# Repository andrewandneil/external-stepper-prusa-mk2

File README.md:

# External Stepper Drivers for Prusa MK2 Based Printers
Adds the ability to use external TMC stepper drivers on the Prusa MK2/S/2.5/S (any printer that uses the Mini Rambo).

## Purpose
Since the Mini Rambo that powers the original line of Prusas was released, stepper driver technology has come a long way. Now days, the `A4982`s that are hard soldered onto the board are louder and less accurate than more modern offerings from `Trinamic`.

The mission of this project is to create an open source PCB ~~and Case~~ design to allow the use of standard, off the shelf stepper driver boards to be used with printers such as the `Prusa MK2/S/2.5/S`. This will allow the printer to run quieter and smoother, resulting in a nicer experience whilst printing, as well as a nicer quality of print.

Achived by utilising the handily placed test points on the back of the Mini Rambo, this board is able to 'steal' the data signals intended for the `A4982`s on the board and give them to the user's choice of stepper drivers.

Side note: if you have a blown driver on your Mini Rambo, this is a great way of getting it up and running again. Simiply solder this board to the pads corresponding to the dead driver on the back of the board, and hey presto, a functional printer again!

Upon seeing a certain other design on the internet that did the same thing, but was closed source, I decided to create my own design from scratch, and make it open source! You will find all KiCAD PCB Design files, along with the F3D files and STEP files for the case I have created. 

## Functionality
Tested mostly with the `TMC2208` drivers, however, `TMC2209`s, `TMC2130`s and `TMC2100`s (may require to be in their 'standalone' mode) have all been tested and confirmed to work with this board and the printer. However, do note the graphic towards the bottom left of the PCB for the correct positioning of the jumpers for your stepper drivers.

Compatible with any printer using the Mini Rambo main board, including but not limited to `Prusa i3 MK2`, `Prusa i3 MK2S`, `Prusa i3 MK2.5` and `Prusa i3 MK2.5S`.

## Utilisation
This WILL require modifying your mainboard. However, the modification is not permant and can be reversed at any time. Only requires soldering to 8 fairly large points on the back of the main board. You will also need to get power for the board from somewhere. To do this you have 2 options:
  1. Tap into the 12V supplied from the printer's power supply and run a cable to the socket on the board.
  2. Run either a 12V or 24V external power supply and utilise that. 

The 24V option is your prefered option if you are wanting the drivers to operate as cool and quite as possible, however, please see the [optional](/Guides/PartsList.md/#optional) section of the parts list for more information.

#### Setting Stepper Current
My `TMC2208`s have been set to a Vref voltage of 1V[^1].

## What's Included?
In the repository you will find the KiCAD files if you wish to modify, adapt or improve the board ~~and a 3D printable case for the board, along with a STEP file if you wish to modify, adapat or improve it.~~ (yet to be added).

Please see the [releases](https://github.com/andrewandneil/external-stepper-prusa-mk2/releases) section to find the current Gerber files for the fabrication of the PCB.

## Software Used
  - [KiCAD](https://kicad.org): An amazing, open source, PCB design studio. I encourage you to check it out if you're looking for something like that. Used to design the schematics, PCB and export the Gerber Files.
  - [Fusion 360](https://www.autodesk.com/products/fusion-360): A good all round CAD software, with a free personal license. ~~Used to design the case.~~

## Pictures
To be added

## Cases

### My Case
As of the moment yet to be finalised

### Other People's Cases
In the offchance that someone either, modifies, redesigns, or creates from sctach a new case or related accessory, I'll do my best to add them here.

If you're one of amazing community that might create a case, get in touch with me and I'll link it here, along with any credit due.

## Parts List
Please see [here](/Guides/PartsList.md).

## Assembly Guide
Please see [here](/Guides/AssemblyGuide.md).

## What else
Notice how nowhere in this guide I mentioned the X and Y axis until now? Well, for good reason. If you wanted to you could build a board for the E and Z axis and use it in parallel to a X and Y board (or just use the E and Z board if you're weird like that I suppose). The Z motor plug will need to be split into 2 new plugs (one for ZL and ZR). The board labels the two sockets with X and Y identifiers, but this is more so you can trace which plug goes where. Obvisouly just connect either the X or Y plugs to the E or Z solder pads on the Rambo if you're planning on doing this.

However, logically with the X and Y axis doing the most moving and at the highest speeds, your best bet to make it mostly quiet is just making one for the X and Y.

## Future Plans
I have no clue if I will ever get around to implementing these plans but you might as well know about them (if I don't do them and you're reading this in the future please feel free to 'borrow' these ideas 😉):
  - Creating a board that allows X, Y, E and Z axis drivers all on one board.
  - Creating a 3D printable case for the board.
  - Test the board with even more drivers.
  - Create an easy to follow and detailed guide for assembly.

## Using these Files
This project is protected by a GNU GPL v3.0 license:
  - You are free to use the files and designs to create your own boards in a personal manner[^2].
  - You are also free to use the files and designs to create boards to sell and make a profit, so long as credit is given or a link is added to this GitHub page[^2].
  - You are also free to modify or otherwise change the files and designs included in anyway you see fit, so long as if the project is shared, it follows the GNU GPL v3.0 license and credit is given[^2].

I fully encourage you to do what you see fit with this design, so long as it follows the GNU license[^2]. If you have the know how and have an idea for an improvement, I look forward to see what you can do! After all, that's the spirit of RepRap!

[^2]:**Not legal adivce. Please read [COPYING.txt](/COPYING.txt) for the full GNU GPL v3.0 license**

## Currently Known Issues
##### Will do my best to update if other issues are found
  - Z and E motors will 'squeal' if using TMC drivers on X and Y axis. I believe this to be something to do with microstepping. Only happens if the motors are powered and at a certain rotational degree. *Your quick fix here is to ignore it or make a board for the E and Z axis*
    - It is completely unnoticable during motion. You will only really hear it if your printer is unlucky enough to stop in a rotaional positon where it happens.

## Disclamer
I have tested this board extensively and have yet to run into issues, however, if you choose to do this mod, you do so at your own risk. I, nor any other party involved, offer any kind of warranty with this product. I have done my best to include all relevant information in this GitHub page, to allow you to come to a decision as to wether or not you would like to partake in this mod. This is not a product. You must source and assemble the board yourself. I will do my best to support any issues you may have if I can.

[^1]: My reference voltage and therefore stepper current is just a suggestion not a defintive do it. Do your own research and experimentation to suit your steppers and drivers.

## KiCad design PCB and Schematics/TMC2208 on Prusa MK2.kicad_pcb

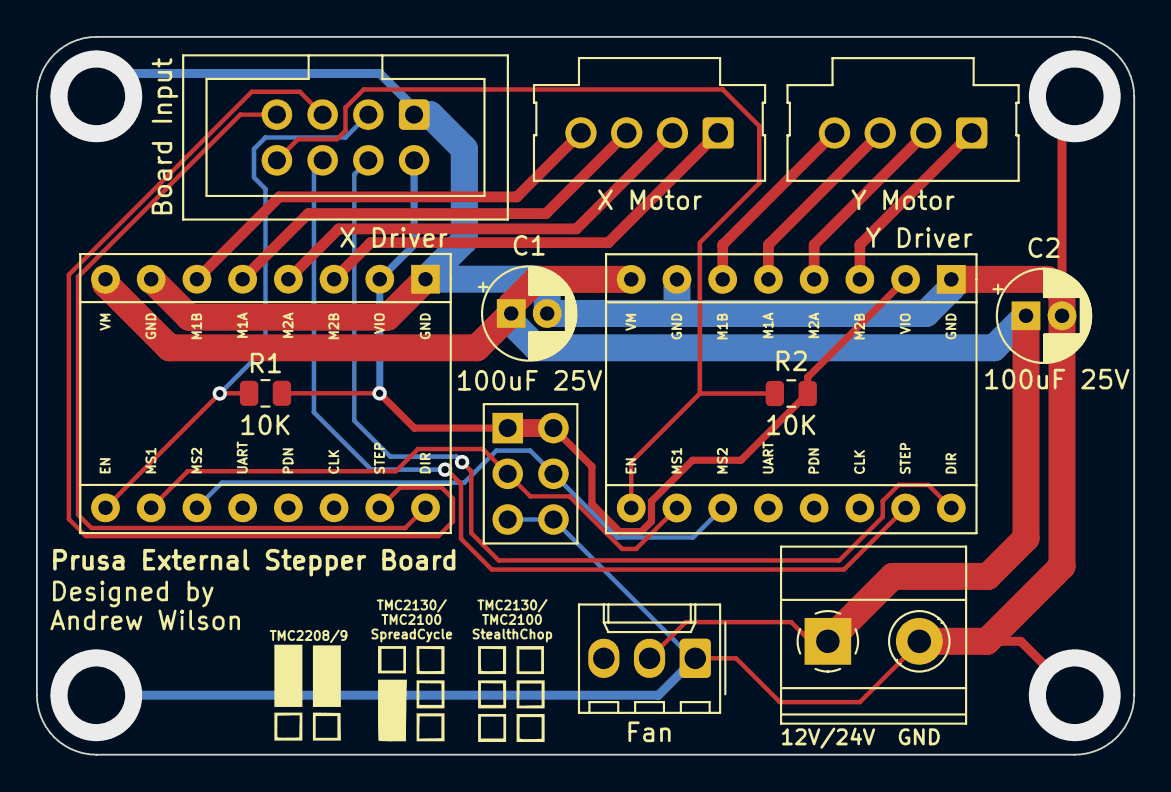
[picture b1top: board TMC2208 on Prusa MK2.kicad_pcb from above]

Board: 2 copper layers, 61.0 x 39.9 mm, 12 parts (0 on the bottom side), 19 nets.

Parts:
Board Input: Conn_02x04_Odd_Even; IDC-Header_2x04_P2.54mm_Vertical
C1, C2: 100uF 25V; CP_Radial_D5.0mm_P2.00mm
Fan: Conn_01x03_Male; Molex_KK-254_AE-6410-03A_1x03_P2.54mm_Vertical
J1: Conn_02x03_Counter_Clockwise; PinHeader_2x03_P2.54mm_Vertical
J4: Screw_Terminal_01x02; TerminalBlock_Phoenix_MKDS-1,5-2-5.08_1x02_P5.08mm_Horizont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
R1, R2: 10K; R_0805_2012Metric
X Motor: Conn_01x04_Male; Molex_SL_171971-0004_1x04_P2.54mm_Vertical
XDriver1: Trinamic_Breakout_TMC2208; Trinamic_Breakout-16_15.2x20.3mm
Y Motor: Conn_01x04_Male; Molex_SL_171971-0004_1x04_P2.54mm_Vertical
YDriver1: Trinamic_Breakout_TMC2208; Trinamic_Breakout-16_15.2x20.3mm

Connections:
+12V: C1.1, C2.1, Fan.2, J4.1, XDriver1.8 (VM), YDriver1.8 (VM)
/CONFIG1: J1.3, XDriver1.10 (MS1), YDriver1.10 (MS1)
/CONFIG2: J1.4, XDriver1.11 (MS2), YDriver1.11 (MS2)
GND: Board Input.1, C1.2, C2.2, Fan.1, J1.5, J1.6, J4.2, XDriver1.1 (GND), XDriver1.7 (GND), YDriver1.1 (GND), YDriver1.7 (GND)
unnamed: Board Input.3, R1.1, XDriver1.9 (~ENABLE)
unnamed: Board Input.4, YDriver1.16 (DIR)
unnamed: Board Input.5, XDriver1.15 (STEP)
unnamed: Board Input.6, YDriver1.15 (STEP)
unnamed: Board Input.7, XDriver1.16 (DIR)
unnamed: Board Input.8, R2.2, YDriver1.9 (~ENABLE)
unnamed: X Motor.1, XDriver1.3 (M2B)
unnamed: X Motor.2, XDriver1.4 (M2A)
unnamed: X Motor.3, XDriver1.5 (M1A)
unnamed: X Motor.4, XDriver1.6 (M1B)
unnamed: Y Motor.1, YDriver1.3 (M2B)
unnamed: Y Motor.2, YDriver1.4 (M2A)
unnamed: Y Motor.3, YDriver1.5 (M1A)
unnamed: Y Motor.4, YDriver1.6 (M1B)
VCC: Board Input.2, J1.1, J1.2, R1.2, R2.1, XDriver1.2 (VIO), YDriver1.2 (VIO)

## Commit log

2023-01-17 Added initial body
2023-01-18 (Hopefully?) Finalised
2023-01-18 Added a required part to be a PCB
2023-01-18 Added PCB and Schematics
2023-01-18 Added new image
